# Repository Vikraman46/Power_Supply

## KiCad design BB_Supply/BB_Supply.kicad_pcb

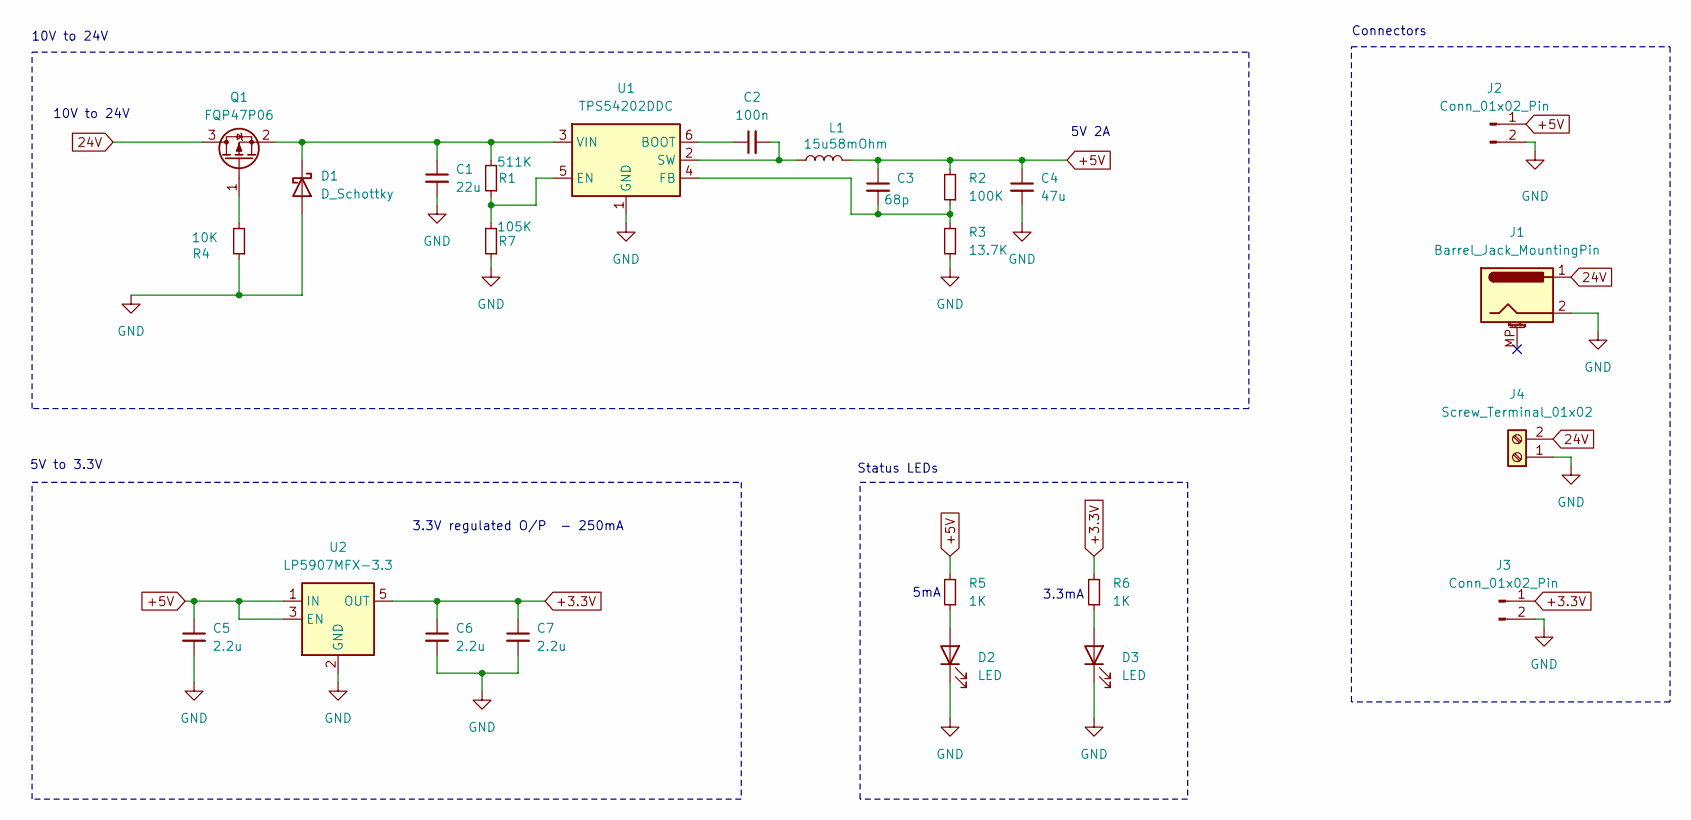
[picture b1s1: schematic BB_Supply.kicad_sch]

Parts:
C1: 22u; C_0603_1608Metric_Pad1.08x0.95mm_HandSolder
C2: 100n; C_0805_2012Metric_Pad1.18x1.45mm_HandSolder
C3: 68p; C_0402_1005Metric_Pad0.74x0.62mm_HandSolder
C4: 47u; C_0805_2012Metric_Pad1.18x1.45mm_HandSolder
C5, C6, C7: 2.2u; C_0603_1608Metric_Pad1.08x0.95mm_HandSolder
D1: D_Schottky; D_SOD-123
D2, D3: LED; LED_0603_1608Metric_Pad1.05x0.95mm_HandSolder
J1: Barrel_Jack_MountingPin; CUI_PJ-002A
J2, J3: Conn_01x02_Pin; PinHeader_1x02_P1.27mm_Vertical
J4: Screw_Terminal_01x02; TerminalBlock_Xinya_XY308-2.54-2P_1x02_P2.54mm_Horizontal
L1: 15u58mOhm; L_Changjiang_FNR5040S
Q1: FQP47P06; TO-220-3_Horizontal_TabDown
R1: 511K; R_0603_1608Metric_Pad0.98x0.95mm_HandSolder
R2: 100K; R_0603_1608Metric_Pad0.98x0.95mm_HandSolder
R3: 13.7K; R_0603_1608Metric_Pad0.98x0.95mm_HandSolder
R4: 10K; R_0603_1608Metric_Pad0.98x0.95mm_HandSolder
R5, R6: 1K; R_0603_1608Metric_Pad0.98x0.95mm_HandSolder
R7: 105K; R_0603_1608Metric_Pad0.98x0.95mm_HandSolder
U1: TPS54202DDC; SOT-23-6_Handsoldering
U2: LP5907MFX-3.3; SOT-23-5

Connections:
24V: J1.1, J4.2, Q1.3 (D); also elsewhere on the board
+3.3V: C6.1, C7.1, J3.1, R6.2, U2.5 (OUT)
+5V: C3.1, C4.1, C5.1, J2.1, L1.2, R2.2, R5.2, U2.1 (IN), U2.3 (EN)
GND: C1.2, C4.2, C5.2, C6.2, C7.2, D1.2 (A), D2.1 (K), D3.1 (K), J1.2, J2.2, J3.2, J4.1, R3.1, R4.1, R7.1, U1.1 (GND), U2.2 (GND)
unnamed 4: C1.1, D1.1 (K), Q1.2 (S), R1.2, U1.3 (VIN); also elsewhere on the board
unnamed: D2.2 (A), R5.1
unnamed: D3.2 (A), R6.1
unnamed 7: Q1.1 (G), R4.2; also elsewhere on the board
unnamed: C2.1, U1.6 (BOOT)
unnamed: R1.1, R7.2, U1.5 (EN)
unnamed: C3.2, R2.1, R3.2, U1.4 (FB)
unnamed: C2.2, L1.1, U1.2 (SW)

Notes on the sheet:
Connectors
5V to 3.3V
5mA
5V 2A
10V to 24V
3.3V regulated O/P - 250mA
3.3mA
10V to 24V
Status LEDs

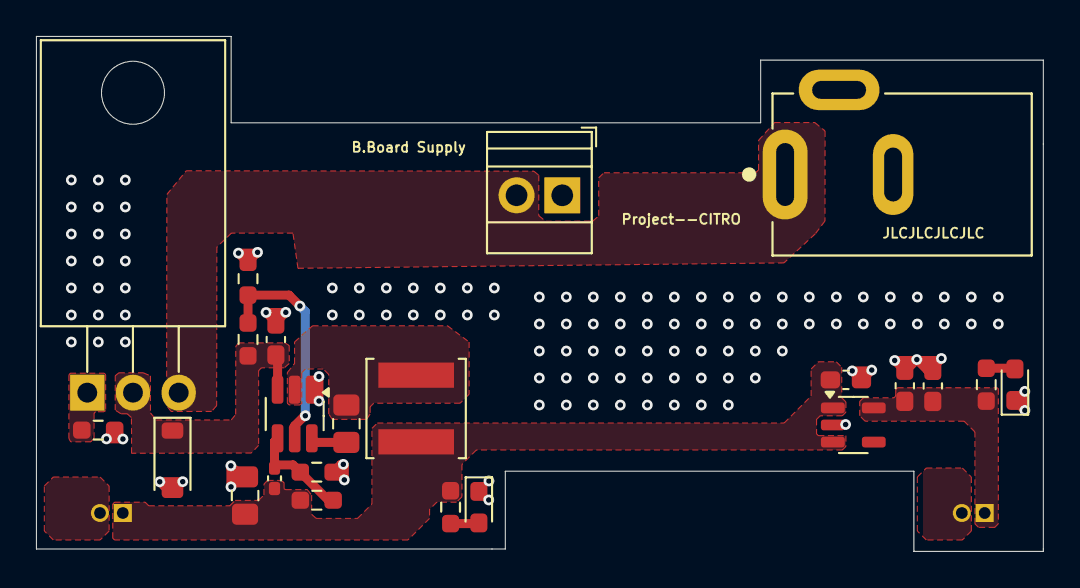
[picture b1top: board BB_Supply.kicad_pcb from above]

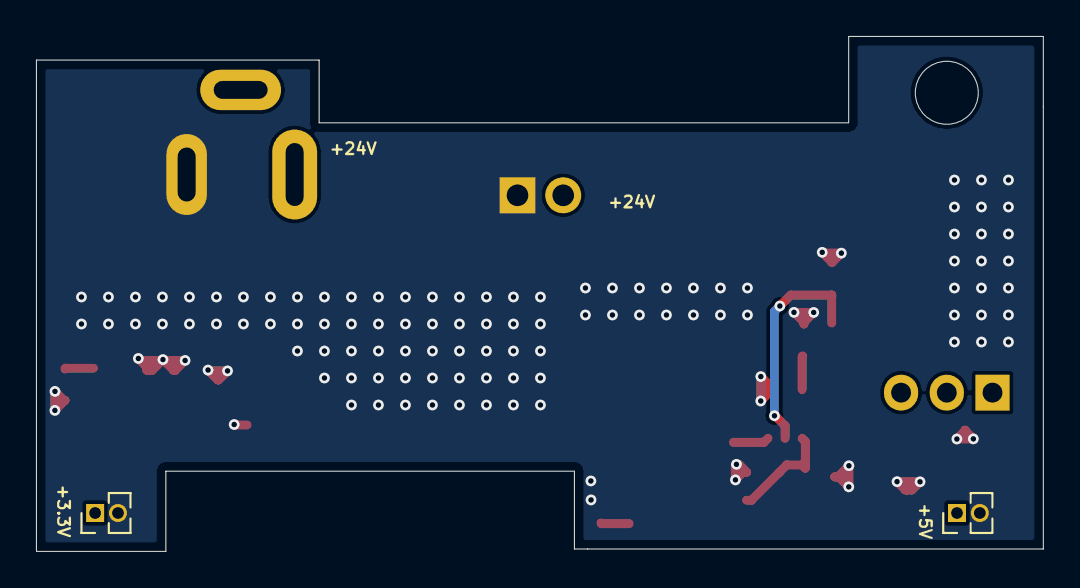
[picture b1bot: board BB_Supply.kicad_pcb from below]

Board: 2 copper layers, 55.9 x 28.6 mm, 25 parts (2 on the bottom side), 12 nets.

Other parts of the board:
Qe: FQP47P06; TO-220-3_Horizontal_TabDown

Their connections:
24V: Qe.3 (D); also elsewhere on the board
unnamed 4: Qe.2 (S); also elsewhere on the board
unnamed 7: Qe.1 (G); also elsewhere on the board

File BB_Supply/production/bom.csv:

Designator,Footprint,Quantity,Value,LCSC Part #
C1,0603,1,22u,
C2,0805,1,100n,
C3,0201,1,68p,
C4,0805,1,47u,
"C5, C6, C7",0603,3,2.2u,
D1,D_SOD-123,1,D_Schottky,
"D2, D3",0603,2,LED,
J1,CUI_PJ-002A,1,Barrel_Jack_MountingPin,
"J2, J3",PinHeader_1x02_P1.27mm_Vertical,2,Conn_01x02_Pin,
J4,TerminalBlock_Xinya_XY308-2.54-2P_1x02_P2.54mm_Horizontal,1,Screw_Terminal_01x02,
L1,L_Changjiang_FNR5040S,1,15u58mOhm,
Q1,TO-220-3_Horizontal_TabDown,1,FQP47P06,
R1,0603,1,511K,
R2,0603,1,100K,
R3,0603,1,13.7K,
R4,0603,1,10K,
"R5, R6",0603,2,1K,
R7,0603,1,105K,
U1,SOT-23-6_Handsoldering,1,TPS54202DDC,
U2,SOT-23-5,1,LP5907MFX-3.3,

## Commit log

2024-11-07 Added Files
